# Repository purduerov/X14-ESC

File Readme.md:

# Readme for X14-ESCs

Whenever you make a new part, download the datasheet and save it here _**and**_ with the part in the parts library

Always pull other people's changes before beginning to work
`git pull`

Be sure to push your changes after  working on them. Run:
1. `git add .` to add any files in this directory or a subdirectory
or `git add -u` to add any modified files
2. (Optional) `git clean -nX` to see what ignored files can be removed
	`git clean -fX` removes ignored files (Eagle backups)
3. `git commit -m "helpful commit message"` with a description of the work that you did
4. `git push` to push your work to github

Other helpful commands
* `git status` says information about modified and staged files
* `git log` shows the recent commits of the repository
* `git log filename.extension` show the recent commits for just that file
* `git checkout first-couple-letter-of-commit-id` lets you go back to a previous version
* `git checkout master` brings you back to the latest commit
* `git tag` lists the tags
* `git tag -a orderX -m "the version of the board placed for the X'th order"` tag a specific commit
* `git push --tags` needed to push tags to remote
* `git show orderX` show the commit log for the given tag
* `git checkout orderX` go back and interact with the files at the tagged commit

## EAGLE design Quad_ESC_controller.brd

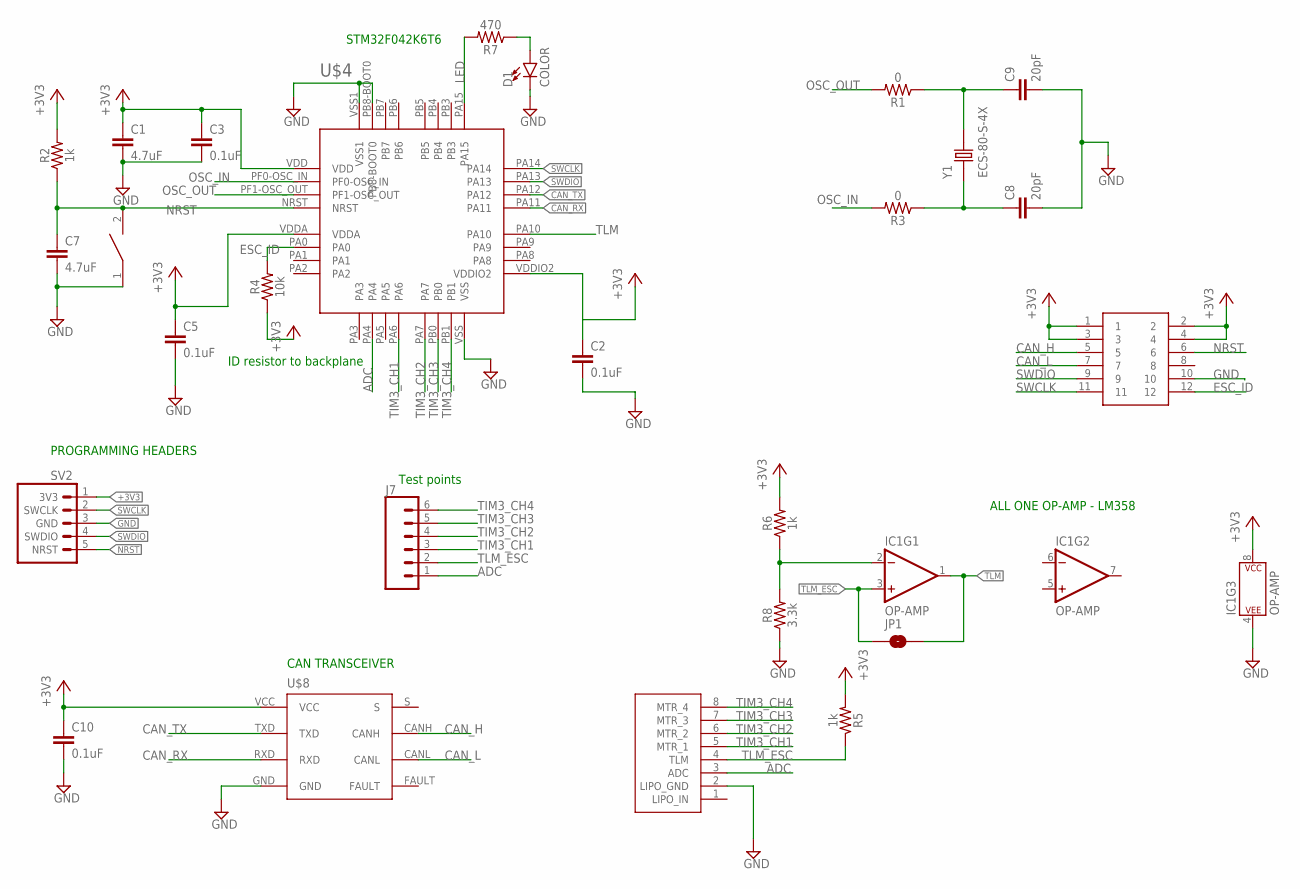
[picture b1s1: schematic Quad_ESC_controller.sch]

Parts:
C1, C7: 4.7uF; 0603
C2, C3, C5, C10: 0.1uF; 0603
C8, C9: 20pF; 0603
D1: COLOR; 0805
IC1: OP-AMP; SO08
J7: CONN_06SILK_FEMALE_PTH; 1X06
JP1: JUMPER-SMT_2_NO_SILK; SMT-JUMPER_2_NO_SILK
R1, R3: 0; 0603
R2, R5, R6: 1k; 0603
R4: 10k; 0603
R7: 470; 0603
R8: 3.3k; 0603
RESET: DISCRETECOMPONENTS_SWITCH; DISCRETECOMPONENTS_SW_2512
SV2: 3V3 -SWCLK-GND-SWDIO- NRST; 1X05
U$2: JST-8PIN; 8PIN_CONNECTOR
U$3: BACKPLANE_CONNECTORSESC; BACKPLANE_CONNECTORS_ESC
U$4: STM32F042K6T6
U$8: TCAN337D
Y1: ECS-80-S-4X; XTAL_ECS-80-S-4X

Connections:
+3V3: C1.1, C2.1, C3.1, C5.1, C10.1, IC1.8 (P$V+), R2.2, R4.1, R5.2, R6.2, SV2.1 (3V3), U$3.1, U$3.2, U$3.3, U$3.4, U$4.VDD, U$4.VDDA, U$4.VDDIO2, U$8.VCC
ADC: J7.1, U$2.3 (ADC), U$4.PA4
CAN_H: U$3.5, U$8.CANH
CAN_L: U$3.7, U$8.CANL
CAN_RX: U$4.PA11, U$8.RXD
CAN_TX: U$4.PA12, U$8.TXD
ESC_ID: R4.2, U$3.12, U$4.PA0
GND: C1.2, C2.2, C3.2, C5.2, C7.2, C8.2, C9.2, C10.2, D1.C, IC1.4 (P$V-), R8.1, RESET.1, SV2.3 (GND), U$2.2 (LIPO_GND), U$3.10, U$4.PB8-BOOT0, U$4.VSS, U$4.VSS1, U$8.GND
LED: R7.2, U$4.PA15
unnamed: C9.1, R1.1, Y1.2
unnamed: C8.1, R3.1, Y1.1
unnamed: IC1.2 (-IN), R6.1, R8.2
unnamed: D1.A, R7.1
NRST: C7.1, R2.1, RESET.2, SV2.5 (NRST), U$3.6, U$4.NRST
OSC_IN: R3.2, U$4.PF0-OSC_IN
OSC_OUT: R1.2, U$4.PF1-OSC_OUT
SWCLK: SV2.2 (SWCLK), U$3.11, U$4.PA14
SWDIO: SV2.4 (SWDIO), U$3.9, U$4.PA13
TIM3_CH1: J7.3, U$2.5 (MTR_1), U$4.PA6
TIM3_CH2: J7.4, U$2.6 (MTR_2), U$4.PA7
TIM3_CH3: J7.5, U$2.7 (MTR_3), U$4.PB0
TIM3_CH4: J7.6, U$2.8 (MTR_4), U$4.PB1
TLM: IC1.1 (OUT), JP1.2, U$4.PA10
TLM_ESC: IC1.3 (+IN), J7.2, JP1.1, R5.1, U$2.4 (TLM)

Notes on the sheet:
STM32F042K6T6
PROGRAMMING HEADERS
CAN TRANSCEIVER
ID resistor to backplane
ALL ONE OP-AMP - LM358
Test points

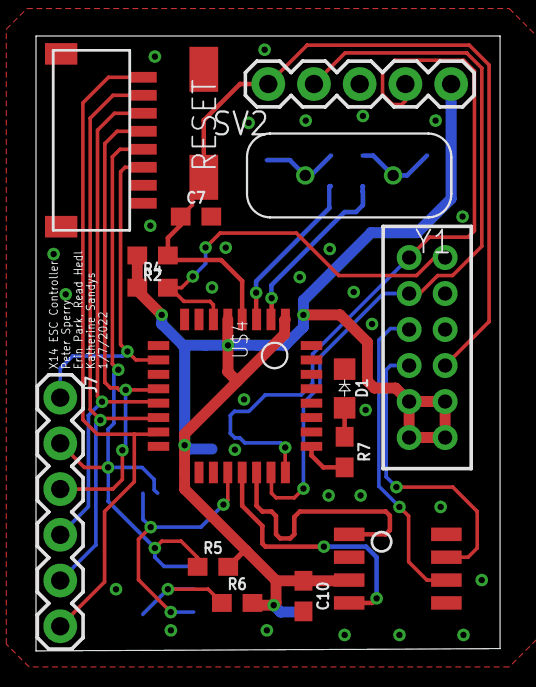
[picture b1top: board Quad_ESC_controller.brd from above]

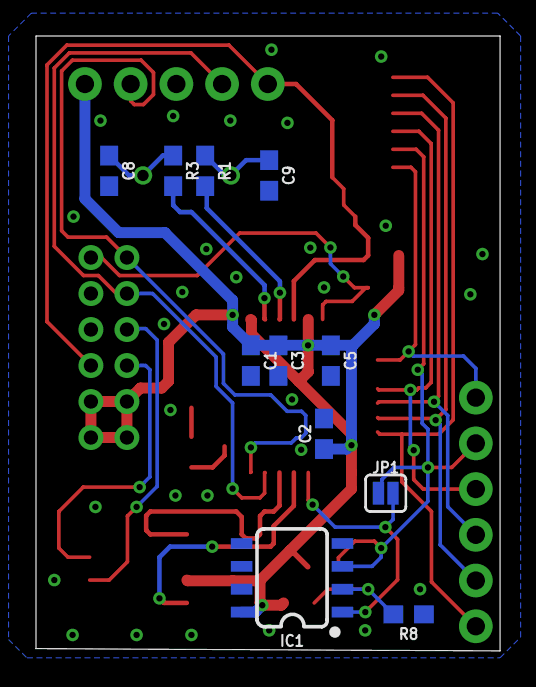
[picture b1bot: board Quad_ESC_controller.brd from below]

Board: 2 copper layers, 25.8 x 34.2 mm, 27 parts (11 on the bottom side), 24 nets.

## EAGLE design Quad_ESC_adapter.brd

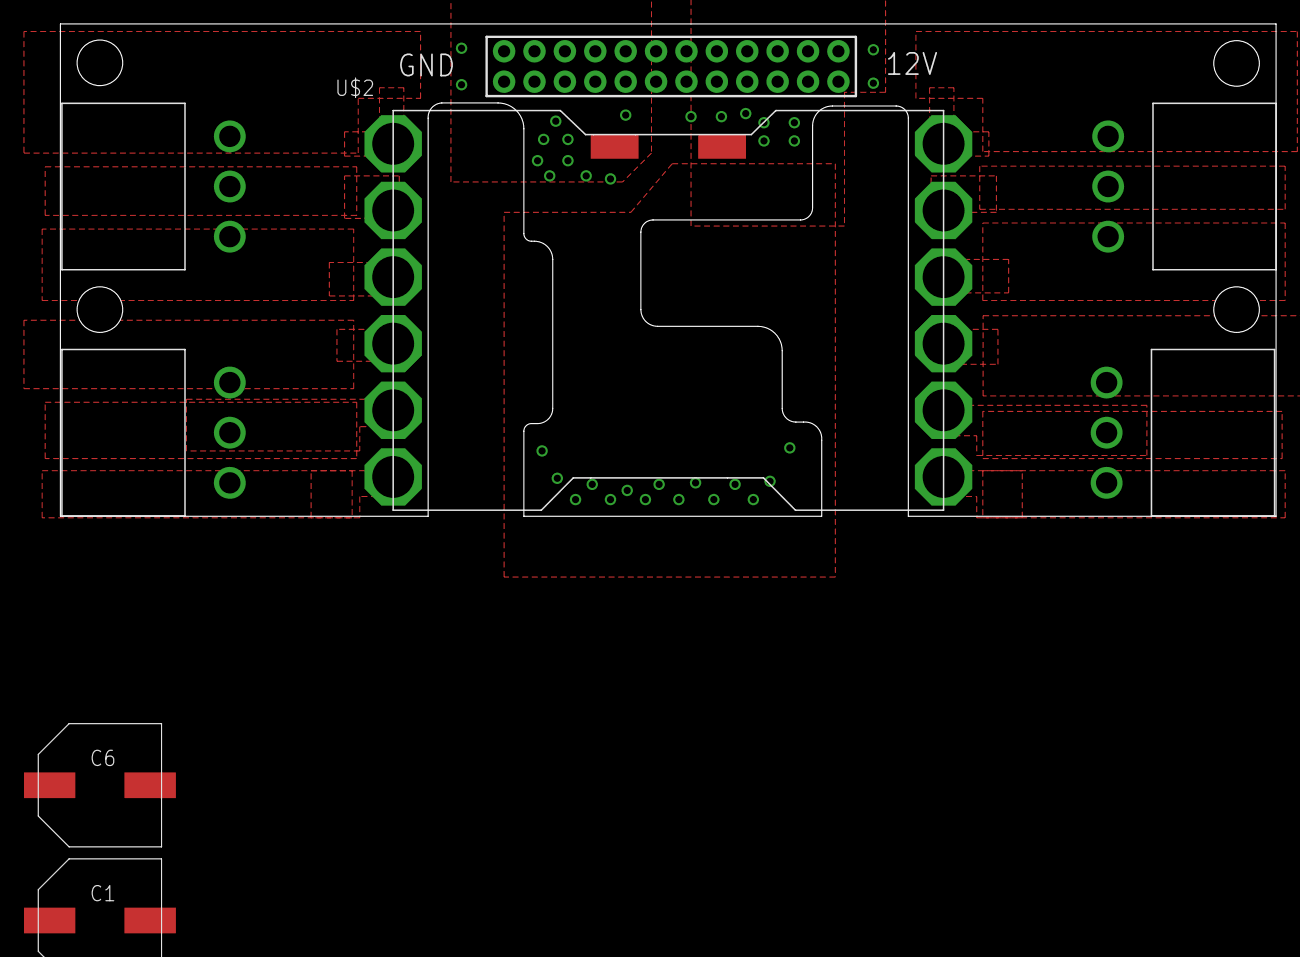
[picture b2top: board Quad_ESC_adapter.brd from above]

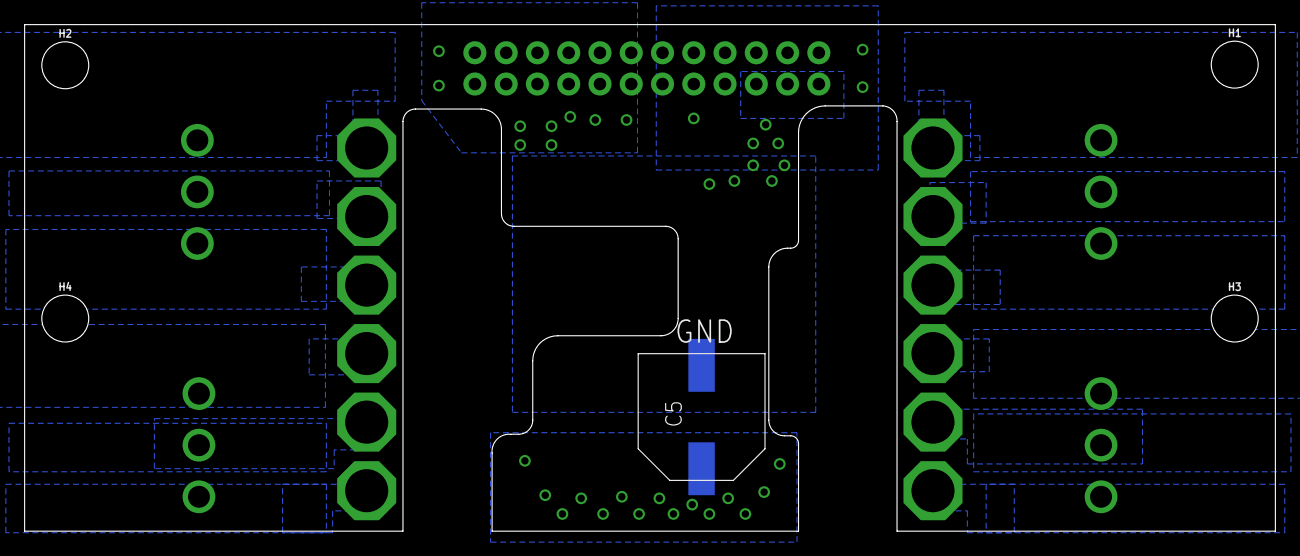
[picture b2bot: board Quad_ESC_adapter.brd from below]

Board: 2 copper layers, 101.6 x 41.1 mm, 13 parts (5 on the bottom side), 14 nets, no tracks yet.

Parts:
C1, C5, C6: 330uF; CAPAE1030X1050N
H1, H2, H3, H4: 6-32-HOLE
J1, J2, J3, J4: IBPD-SOCKET; IPBD-03-S-K
U$2: BACKPLANE_ESC_ADAPTER_PWRESC; BACKPLANE_ESC_ADAPTER_ESC_PWR
U$10: LUMENIER_QUAD-NO-CUT

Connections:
12V: C1.+, C5.+, C6.+, U$2.12V@1, U$2.12V@2, U$2.12V@3, U$2.12V@4, U$2.12V@5, U$2.12V@6, U$2.12V@7, U$2.12V@8, U$2.12V@9, U$2.12V@10, U$2.12V@11, U$2.12V@12, U$10.VIN
ESC1_B: J1.3, U$10.1
ESC1_R: J1.1, U$10.3
ESC1_Y: J1.2, U$10.2
ESC2_B: J2.3, U$10.4
ESC2_R: J2.1, U$10.6
ESC2_Y: J2.2, U$10.5
ESC3_B: J3.1, U$10.12
ESC3_R: J3.3, U$10.10
ESC3_Y: J3.2, U$10.11
ESC4_B: J4.1, U$10.9
ESC4_R: J4.3, U$10.7
ESC4_Y: J4.2, U$10.8
GND: C1.-, C5.-, C6.-, U$2.GND@1, U$2.GND@2, U$2.GND@3, U$2.GND@4, U$2.GND@5, U$2.GND@6, U$2.GND@7, U$2.GND@8, U$2.GND@9, U$2.GND@10, U$2.GND@11, U$2.GND@12, U$10.GND

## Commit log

2021-09-18 readme+gitignore
2021-10-06 Just a start
2021-10-13 Final touches
2021-10-23 Added status of chips
2021-11-13 changed connectors
2021-11-13 added the LM2904
2021-11-13 added test points
2021-11-18 add board size
2021-11-29 Example placement for adapter
2021-12-01 moved stuff around
2021-12-03 Finalized as best I could
2021-12-03 Routed some ish
2021-12-04 thicc copper
2021-12-04 routed airwires
2021-12-04 done bish
2021-12-04 isolated that ish
2021-12-04 made test points nice
2021-12-11 check this
2022-01-07 added silkscreen, removed caps
2022-01-26 STEPS!
2022-03-10 fixed stupid jumper under chip mistake
2022-03-10 fixed jumper under da chip
2022-03-10 made it nice

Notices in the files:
parts and their libraries:
SparkFun-Aesthetics: Licensing: Creative Commons ShareAlike 4.0 International - https://creativecommons.org/licenses/by-sa/4.0
